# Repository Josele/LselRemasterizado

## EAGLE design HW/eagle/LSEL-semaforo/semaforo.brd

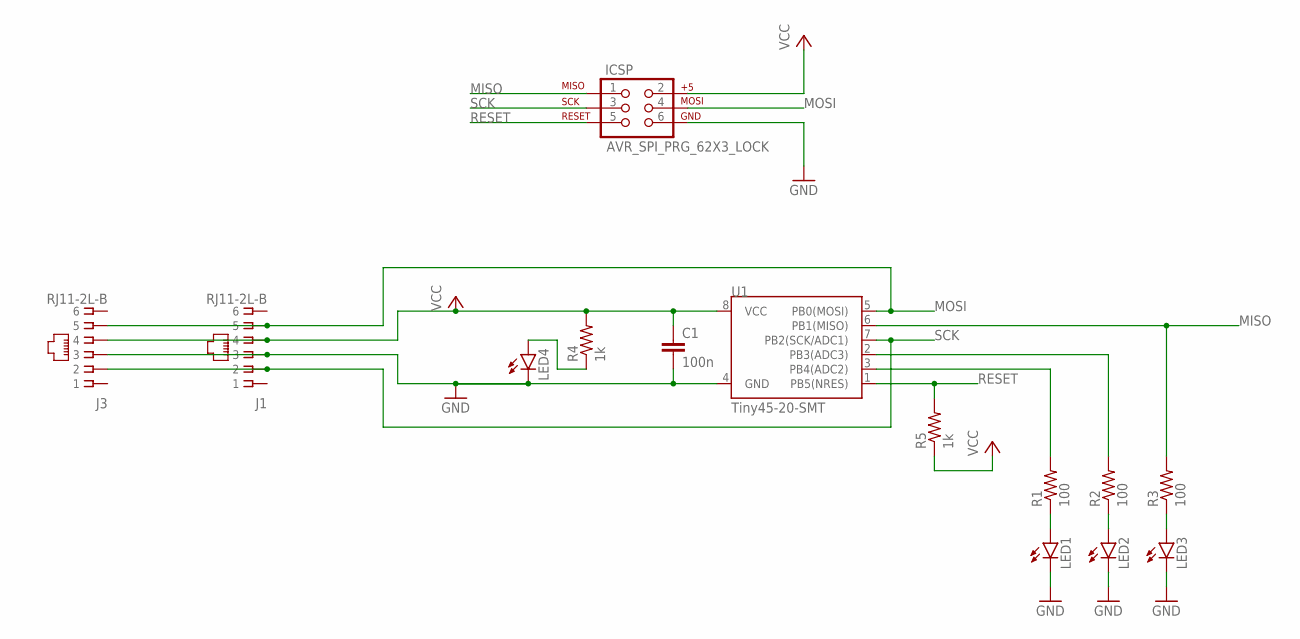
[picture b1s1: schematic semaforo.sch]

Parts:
C1: 100n; 1206
ICSP: AVR_SPI_PRG_62X3_LOCK; 2X3_LOCK
J1, J3: RJ11-2L-B; RJ11-NO_SHIELD
LED1, LED2, LED3: LED5MM
LED4: LED1206; LED-1206
R1, R2, R3: 100; 1206
R4, R5: 1k; 1206
U1: Tiny45-20-SMT; SO08-EIAJ

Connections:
GND: C1.2, ICSP.6, J1.3, J3.3, LED1.K (C), LED2.K (C), LED3.K (C), LED4.C, U1.4 (GND)
MISO: ICSP.1, R3.2, U1.6 (PB1(MISO))
MOSI: ICSP.4, J1.5, J3.5, U1.5 (PB0(MOSI))
unnamed: R1.2, U1.3 (PB4(ADC2))
unnamed: R2.2, U1.2 (PB3(ADC3))
unnamed: LED4.A, R4.1
unnamed: LED1.A, R1.1
unnamed: LED2.A, R2.1
unnamed: LED3.A, R3.1
RESET: ICSP.5, R5.2, U1.1 (PB5(NRES))
SCK: ICSP.3, J1.2, J3.2, U1.7 (PB2(SCK/ADC1))
VCC: C1.1, ICSP.2, J1.4, J3.4, R4.2, R5.1, U1.8 (VCC)

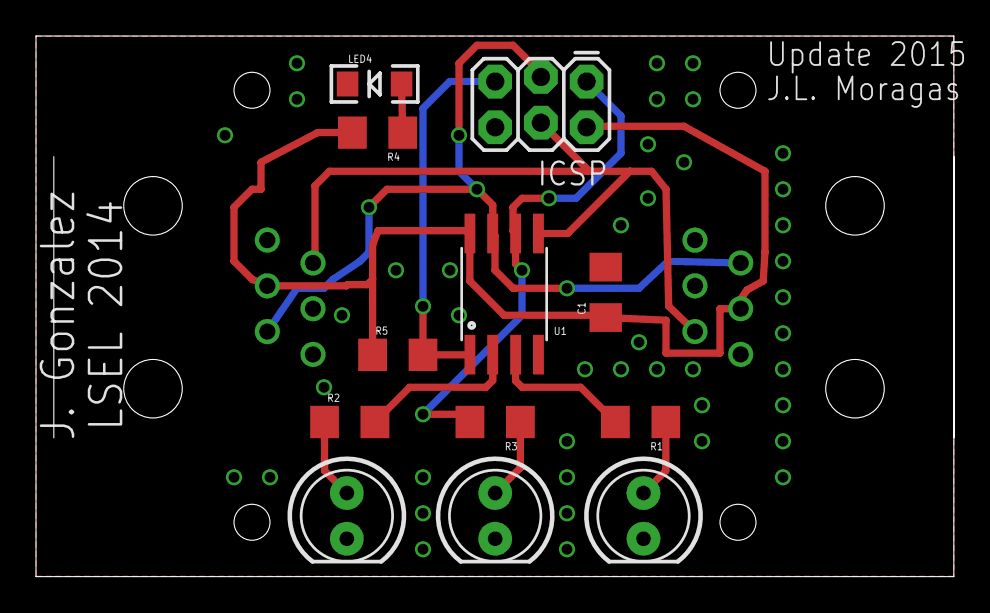
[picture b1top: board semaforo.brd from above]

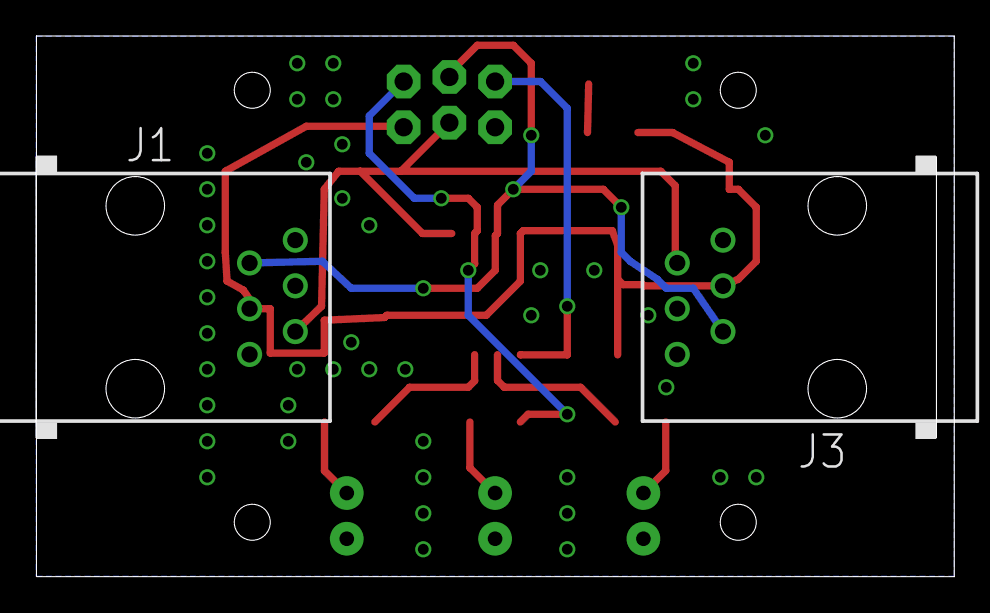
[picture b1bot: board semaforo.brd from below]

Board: 2 copper layers, 51.0 x 30.0 mm, 14 parts (2 on the bottom side), 12 nets.

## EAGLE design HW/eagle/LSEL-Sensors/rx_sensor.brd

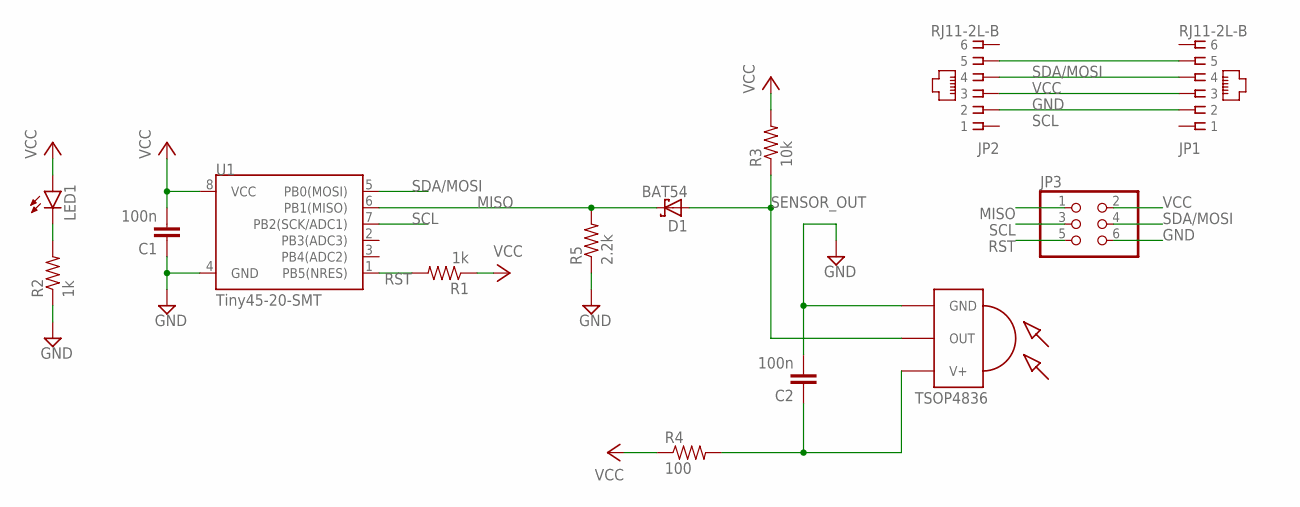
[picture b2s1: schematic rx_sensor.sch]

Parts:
C1, C2: 100n; 0603-CAP
D1: BAT54; SOT23
JP1, JP2: RJ11-2L-B; RJ11-NO_SHIELD
JP3: PINHD-2X3; 2X03
LED1: LED0603; LED-0603
R1, R2: 1k; 0603-RES
R3: 10k; 0603-RES
R4: 100; 0603-RES
R5: 2.2k; 0603-RES
TSOP4836: TSOP4836; TSOP18XX
U1: Tiny45-20-SMT; SO08-EIAJ

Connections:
GND: C1.1, C2.2, JP1.3, JP2.3, JP3.6, R2.1, R5.1, TSOP4836.GND, U1.4 (GND)
MISO: D1.3 (C), JP3.1, R5.2, U1.6 (PB1(MISO))
unnamed: LED1.C, R2.2
unnamed: C2.1, R4.2, TSOP4836.VCC (V+)
RST: JP3.5, R1.2, U1.1 (PB5(NRES))
SCL: JP1.2, JP2.2, JP3.3, U1.7 (PB2(SCK/ADC1))
SDA/MOSI: JP1.5, JP2.5, JP3.4, U1.5 (PB0(MOSI))
SENSOR_OUT: D1.1 (A), R3.1, TSOP4836.OUT
VCC: C1.2, JP1.4, JP2.4, JP3.2, LED1.A, R1.1, R3.2, R4.1, U1.8 (VCC)

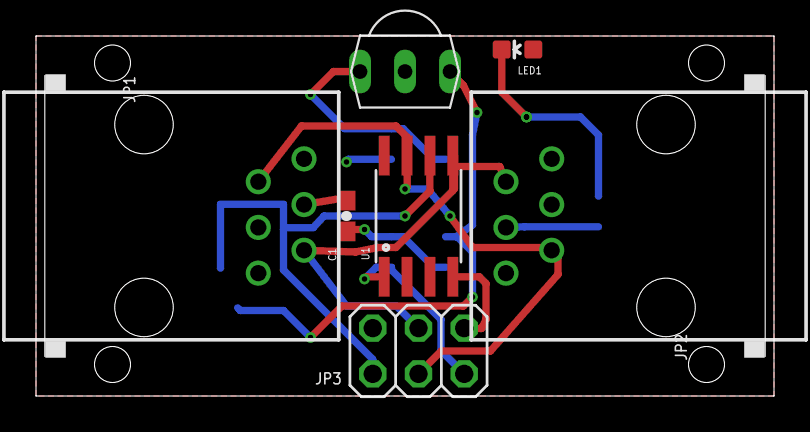
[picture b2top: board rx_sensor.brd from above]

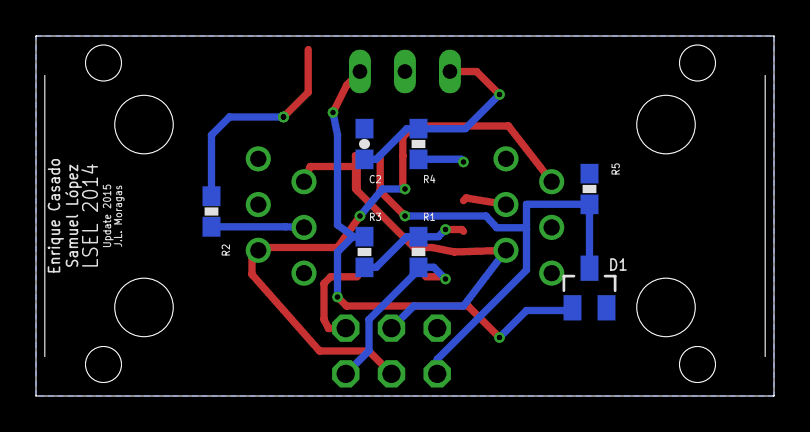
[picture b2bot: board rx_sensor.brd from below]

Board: 4 copper layers, 41.0 x 20.0 mm, 14 parts (7 on the bottom side), 9 nets.

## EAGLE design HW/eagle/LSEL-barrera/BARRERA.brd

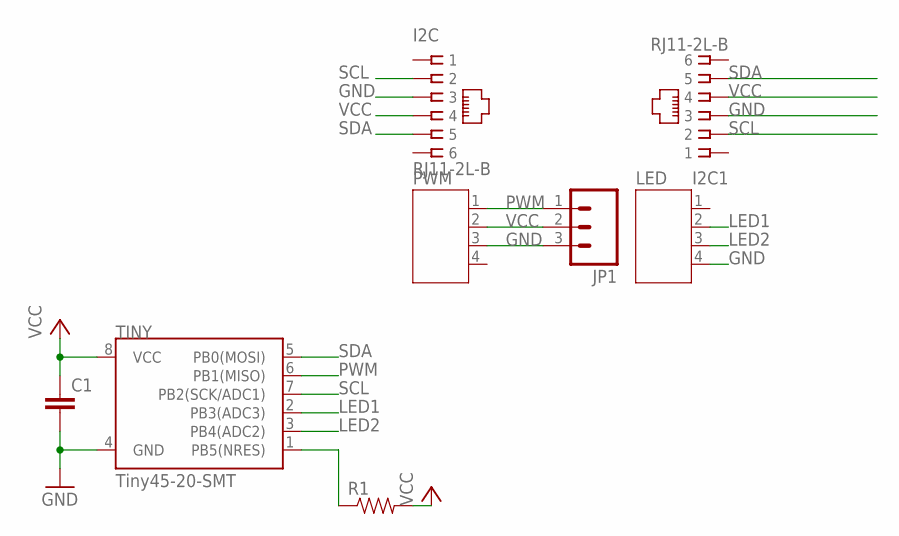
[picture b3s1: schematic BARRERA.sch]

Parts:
C1: CAP0603-CAP; 0603-CAP
I2C, I2C1: RJ11-2L-B; RJ11-NO_SHIELD
JP1: M03PTH; 1X03
LED: JST-PH4
PWM: JST-PH4
R1: RESISTOR0603; 0603-RES
TINY: Tiny45-20-SMT; SO08-EIAJ

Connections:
GND: C1.2, I2C.3, I2C1.3, JP1.3, LED.4, PWM.3, TINY.4 (GND)
LED1: LED.2, TINY.2 (PB3(ADC3))
LED2: LED.3, TINY.3 (PB4(ADC2))
unnamed: R1.1, TINY.1 (PB5(NRES))
PWM: JP1.1, PWM.1, TINY.6 (PB1(MISO))
SCL: I2C.2, I2C1.2, TINY.7 (PB2(SCK/ADC1))
SDA: I2C.5, I2C1.5, TINY.5 (PB0(MOSI))
VCC: C1.1, I2C.4, I2C1.4, JP1.2, PWM.2, R1.2, TINY.8 (VCC)

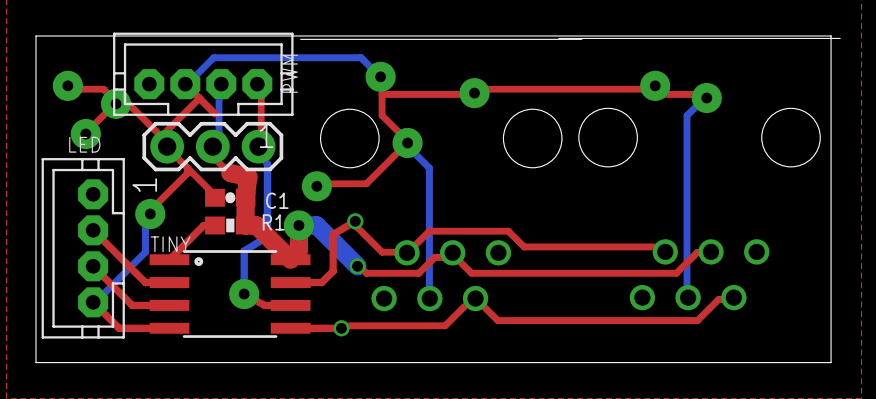
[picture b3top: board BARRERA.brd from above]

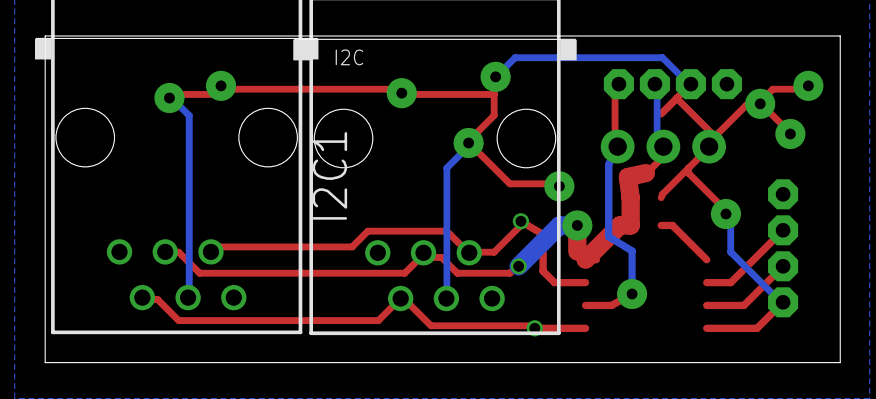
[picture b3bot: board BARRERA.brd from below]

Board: 2 copper layers, 44.7 x 18.1 mm, 8 parts (2 on the bottom side), 8 nets.

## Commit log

2015-05-25 :neckbeard: Added .gitattributes & .gitignore files
2015-05-25 Lsel2014
    antiguo proyecto lsel
2015-05-25 Revert "Lsel2014"
    This reverts commit 244a656e114bcba3e8cbd467e9786478607e89a8.
2015-05-25 Revert "Revert "Lsel2014""
    This reverts commit c0fedd852f2de2bf22f8398f17a69cf75f829897.
2015-05-25 I2C port change
2015-05-25 screen commented
    This raspberry pi doesn't have support for this module
2015-05-25 sun commented
2015-05-26 Original shields
    some changes in the IR RX
2015-05-26 RJ first try
2015-05-26 Documents
    datasheets, RJ information
2015-05-27 Sensor RJ
    Sensor connectors changed
2015-05-27 Sensor IR
    little changes
2015-05-27 Semaforo RJ changed
    Connector were changed
2015-05-27 Barrera RJ changed
2015-05-27 Sensor IR RJ changed
2015-05-27 delete
2015-05-27 Semaforo RJ changed
    correction of mistakes
2015-05-30 Securedaemon
2015-06-01 Gerbers_barrera
2015-06-01 Gerbers rx Sensors
2015-06-01 conexion of the cmd is done through Sockets
2015-06-01 start working
2015-06-01 little changes
2015-06-15 port 4500
2015-06-16 port changed
2015-06-16 l. c.
2015-11-04 changed port
2015-11-08 nothing important
2015-11-09 Run the c program at the same time as the node server
2015-11-09 fsm has changed, support to responses
2015-11-09 add socket answer to some basic commands
2015-11-10 i2ctester added
2015-11-10 nothing
2015-11-10 fixing problems
2015-11-10 10 11 2015
2015-11-12 12/11/2015
2015-12-14 14/12/15
2015-12-23 working all
2015-12-27 mutex in Server and new handlers
2015-12-28 socket real unix
2015-12-30 mix of v2 and first one
2015-12-31 mixing Socketinterp_v3 with 4
2016-01-04 mixing different versions

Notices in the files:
parts and their libraries:
SparkFun-DigitalIC: Licensing: Creative Commons ShareAlike 4.0 International - https://creativecommons.org/licenses/by-sa/4.0
SparkFun: Licensing: CC v3.0 Share-Alike You are welcome to use this library for commercial purposes.
